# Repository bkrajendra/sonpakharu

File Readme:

##README
./hardware - PCB design files
./software - Firmware source code

To open source code:
cd software
code .

To open PCB design:
cd hardware
Open the sonpakharu.kicad_pro file with KiCad

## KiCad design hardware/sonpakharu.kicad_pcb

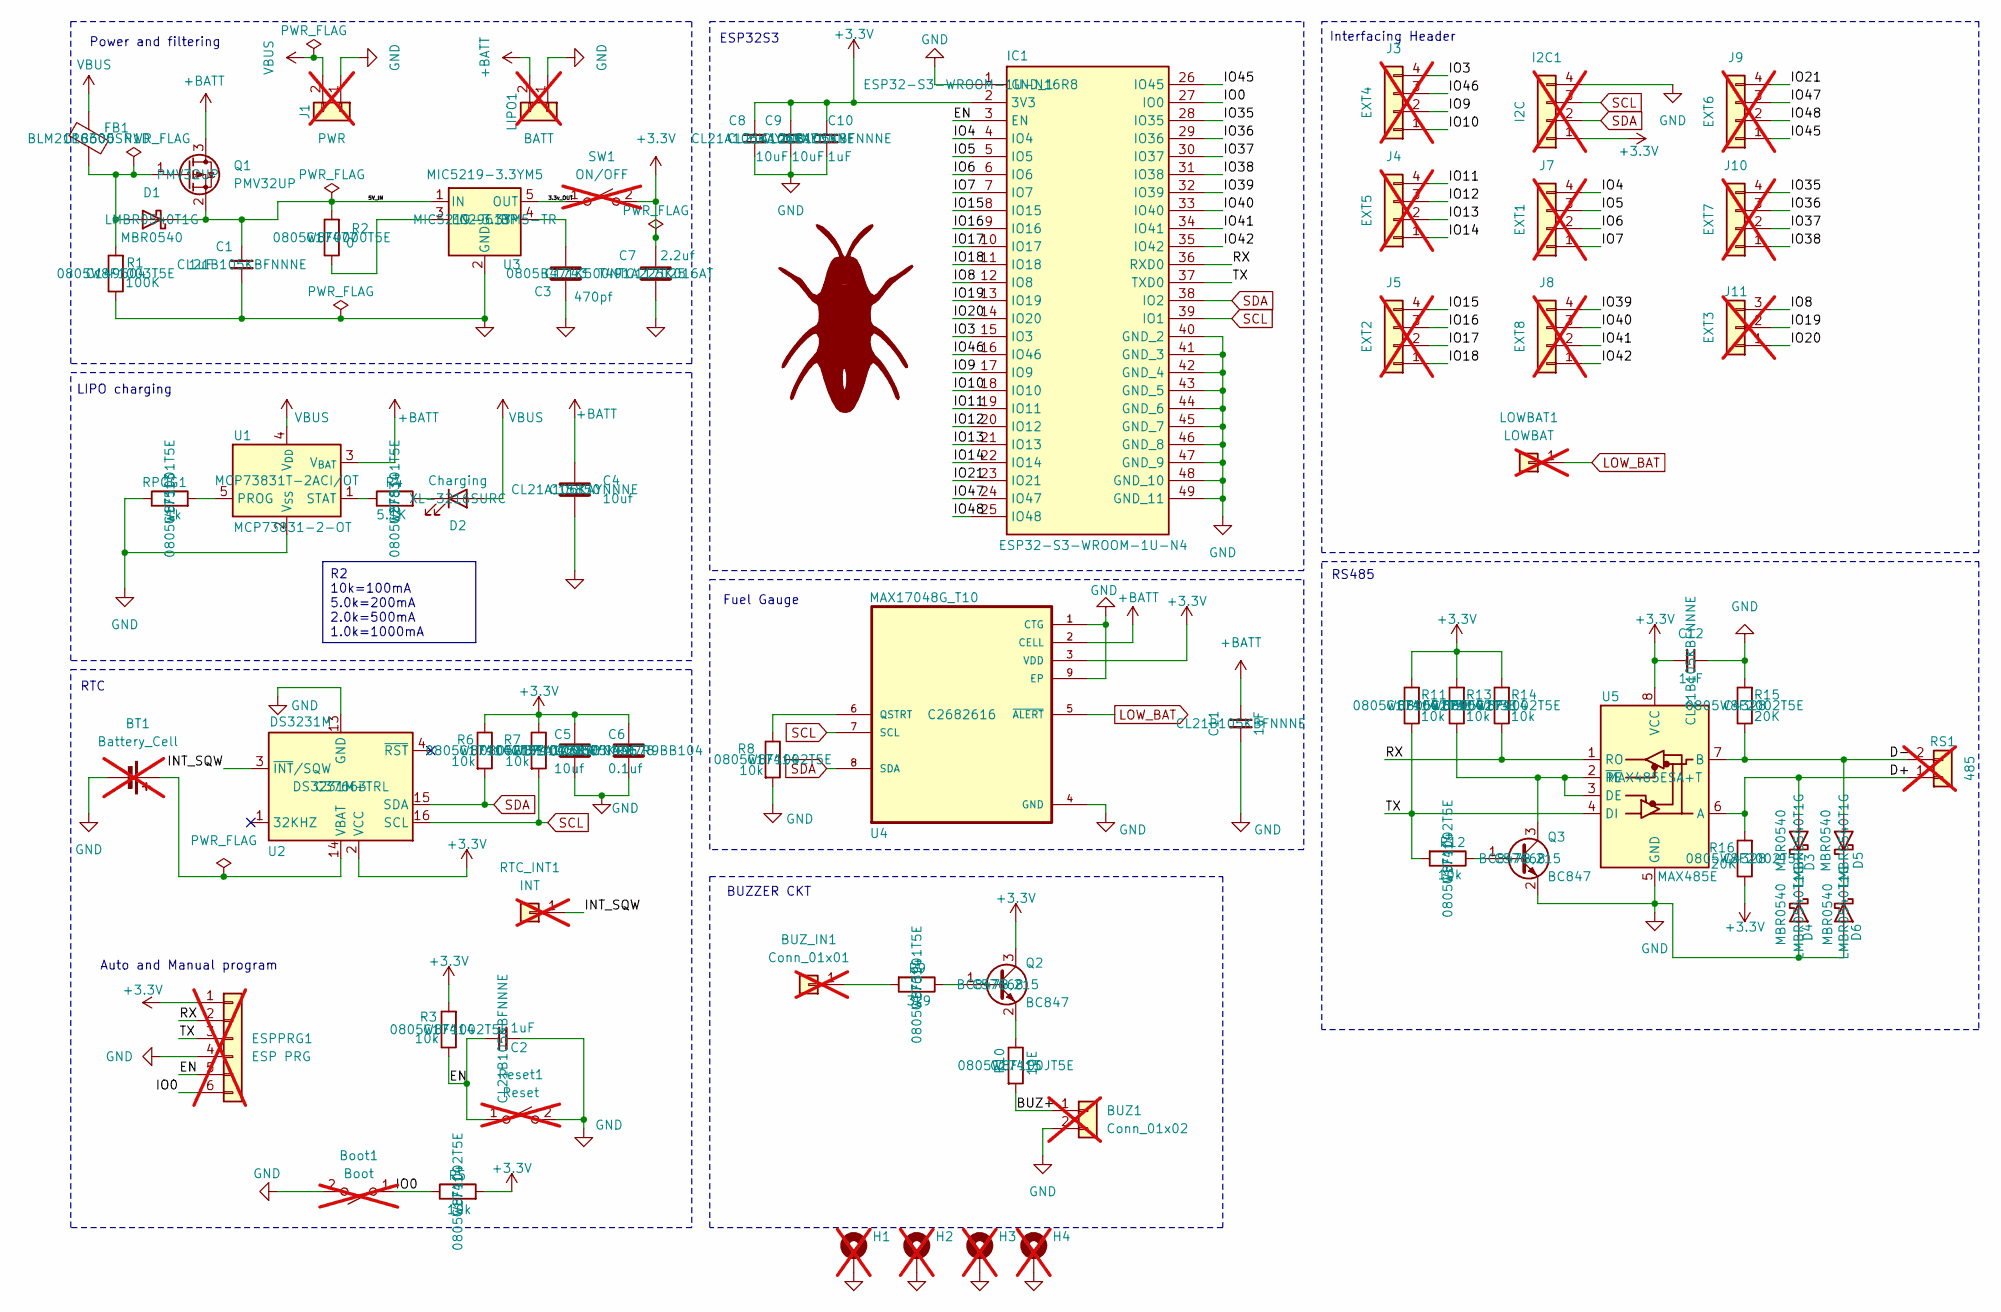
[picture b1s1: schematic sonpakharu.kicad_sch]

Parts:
BT1: Battery_Cell; BatteryHolder_Keystone_3002_1x2032; not fitted
BUZ1: Conn_01x02; PinHeader_1x02_P2.54mm_Vertical; not fitted
BUZ_IN1: Conn_01x01; PinHeader_1x01_P2.54mm_Vertical; not fitted
Boot1: Boot; TACTILE SWITCH 3X4X2MM SMD; not fitted
C1, C2, C10, C11, C12: 1uF; C_0805_2012Metric; MPN C28323
C3: 470pf; C_0805_2012Metric; MPN C1743
C4, C5: 10uf; C_0805_2012Metric; MPN C15850
C6: 0.1uf; C_0805_2012Metric; MPN C49678
C7: 2.2uf; CP_EIA-2012-12_Kemet-R_Pad1.30x1.05mm_HandSolder; MPN C117025
C8, C9: 10uF; C_0805_2012Metric; MPN C15850
D1, D3, D4, D5, D6: MBR0540; D_SOD-123; MPN C78545
D2: Charging; LED_1206_3216Metric; MPN C965822
ESPPRG1: ESP PRG; PinHeader_1x06_P2.54mm_Vertical; not fitted
FB1: FerriteBead; L_0805_2012Metric; MPN C18305
H1, H2, H4: MountingHole_Pad; MountingHole_3mm_Pad_Via; not fitted
H3: mounting hole; MountingHole_3mm_Pad_Via; not fitted
I2C1: I2C; PinHeader_1x04_P2.54mm_Vertical; not fitted
IC1: ESP32-S3-WROOM-1U-N4; ESP32S3WROOM1UN4; Manufacturer_Part_Number ESP32-S3-WROOM-1U-N4; Mouser Part Number 356-ESP32S3WROOM1UN4
J1: PWR; PinHeader_1x02_P2.54mm_Vertical; not fitted
J3: EXT4; PinHeader_1x04_P2.54mm_Vertical; not fitted
J4: EXT5; PinHeader_1x04_P2.54mm_Vertical; not fitted
J5: EXT2; PinHeader_1x04_P2.54mm_Vertical; not fitted
J7: EXT1; PinHeader_1x04_P2.54mm_Vertical; not fitted
J8: EXT8; PinHeader_1x04_P2.54mm_Vertical; not fitted
J9: EXT6; PinHeader_1x04_P2.54mm_Vertical; not fitted
J10: EXT7; PinHeader_1x04_P2.54mm_Vertical; not fitted
J11: EXT3; PinHeader_1x03_P2.54mm_Vertical; not fitted
LIPO1: BATT; PinHeader_1x02_P2.54mm_Vertical; not fitted
LOWBAT1: LOWBAT; PinHeader_1x01_P2.54mm_Vertical; not fitted
Q1: PMV32UP; SOT-23; MPN C2959851
Q2, Q3: BC847; SOT-23; MPN C57668
R1: 100K; R_0805_2012Metric; MPN C149504
R2: 0; R_0805_2012Metric; MPN C17477
R3, R5, R6, R7, R8, R11, R12, R13, R14: 10k; R_0805_2012Metric; MPN C17414
R4: 5.1K; R_0805_2012Metric; MPN C27834
R9: 3k9; R_0805_2012Metric; MPN C17614
R10: 10E; R_0805_2012Metric; MPN C17415
R15, R16: 20K; R_0805_2012Metric; MPN C4328
RPOG1: 1k; R_0805_2012Metric; MPN C17513
RS1: 485; PinHeader_1x02_P2.54mm_Vertical; not fitted
RTC_INT1: INT; PinHeader_1x01_P2.54mm_Vertical; not fitted
Reset1: Reset; TACTILE SWITCH 3X4X2MM SMD; not fitted
SW1: ON/OFF; PinHeader_1x02_P2.54mm_Vertical; not fitted
U1: MCP73831-2-OT; SOT-23-5; MPN C424093
U2: DS3231M; SOIC-16W_7.5x10.3mm_P1.27mm; MPN C37663
U3: MIC5219-3.3YM5; SOT-23-5; MPN C29613
U4: MAX17048G_T10; SON50P200X200X80-9N; MPN C2682616
U5: MAX485E; SOIC-8_3.9x4.9mm_P1.27mm; MPN C19738

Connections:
+3.3V: C5.1, C6.1, C7.1, C8.1, C9.1, C10.1, C12.2, ESPPRG1.1, I2C1.1, IC1.2 (3V3), Q2.3 (C), R3.2, R5.2, R6.1, R7.1, R11.2, R13.2, R14.2, R16.1, SW1.2 (B), U2.2 (VCC), U4.3 (VDD), U5.8 (VCC)
+BATT: C4.1, C11.1, LIPO1.2, Q1.3 (D), U1.3 (V_{BAT}), U4.2 (CELL)
/3.3v_OUT: SW1.1 (A), U3.5 (OUT)
/5V_IN: C1.1, D1.1 (K), Q1.2 (S), R2.2, U3.1 (IN)
/BUZ+: BUZ1.1, R10.2
/D+: D3.2 (A), R16.2, RS1.1, U5.6 (A); also elsewhere on the board
/D-: D5.2 (A), R15.1, RS1.2, U5.7 (B); also elsewhere on the board
/EN: C2.1, ESPPRG1.5, IC1.3 (EN), R3.1, Reset1.1 (A)
/INT_SQW: RTC_INT1.1, U2.3 (~INT/SQW)
/IO0: Boot1.1 (A), ESPPRG1.6, IC1.27 (IO0), R5.1
/IO3: IC1.15 (IO3), J3.4
/IO4: IC1.4 (IO4), J7.4
/IO5: IC1.5 (IO5), J7.3
/IO6: IC1.6 (IO6), J7.2
/IO7: IC1.7 (IO7), J7.1
/IO8: IC1.12 (IO8), J11.3
/IO9: IC1.17 (IO9), J3.2
/IO10: IC1.18 (IO10), J3.1
/IO11: IC1.19 (IO11), J4.4
/IO12: IC1.20 (IO12), J4.3
/IO13: IC1.21 (IO13), J4.2
/IO14: IC1.22 (IO14), J4.1
/IO15: IC1.8 (IO15), J5.4
/IO16: IC1.9 (IO16), J5.3
/IO17: IC1.10 (IO17), J5.2
/IO18: IC1.11 (IO18), J5.1
/IO19: IC1.13 (IO19), J11.2
/IO20: IC1.14 (IO20), J11.1
/IO21: IC1.23 (IO21), J9.4
/IO35: IC1.28 (IO35), J10.4
/IO36: IC1.29 (IO36), J10.3
/IO37: IC1.30 (IO37), J10.2
/IO38: IC1.31 (IO38), J10.1
/IO39: IC1.32 (IO39), J8.4
/IO40: IC1.33 (IO40), J8.3
/IO41: IC1.34 (IO41), J8.2
/IO42: IC1.35 (IO42), J8.1
/IO45: IC1.26 (IO45), J9.1
/IO46: IC1.16 (IO46), J3.3
/IO47: IC1.24 (IO47), J9.3
/IO48: IC1.25 (IO48), J9.2
/RX: ESPPRG1.2, IC1.36 (RXD0), R14.1, U5.1 (RO)
/TX: ESPPRG1.3, IC1.37 (TXD0), R11.1, R12.2, U5.4 (DI)
GND: BT1.2 (-), BUZ1.2, Boot1.2 (B), C1.2, C2.2, C3.2, C4.2, C5.2, C6.2, C7.2, C8.2, C9.2, C10.2, C11.2, C12.1, D4.2 (A), D6.2 (A), ESPPRG1.4, H1.1, H2.1, H3.1, H4.1, I2C1.4, IC1.1 (GND_1), IC1.40 (GND_2), IC1.41 (GND_3), IC1.42 (GND_4), IC1.43 (GND_5), IC1.44 (GND_6), IC1.45 (GND_7), IC1.46 (GND_8), IC1.47 (GND_9), IC1.48 (GND_10), IC1.49 (GND_11), J1.1, LIPO1.1, Q3.2 (E), R1.1, R8.2, R15.2, RPOG1.1, Reset1.2 (B), U1.2 (V_{SS}), U2.5 (GND), U2.6 (GND), U2.7 (GND), U2.8 (GND), U2.9 (GND), U2.10 (GND), U2.11 (GND), U2.12 (GND), U2.13 (GND), U3.2 (GND), U4.1 (CTG), U4.4 (GND), U4.9 (EP), U5.5 (GND)
LOW_BAT: LOWBAT1.1, U4.5 (~ALERT); also elsewhere on the board
unnamed: BT1.1 (+), U2.14 (VBAT)
unnamed 46: BUZ_IN1.1, R9.2; also elsewhere on the board
unnamed 47: D1.2 (A), FB1.2, Q1.1 (G), R1.2; also elsewhere on the board
unnamed: D2.1 (K), R4.2
unnamed: D3.1 (K), D4.1 (K)
unnamed: D5.1 (K), D6.1 (K)
unnamed: Q2.1 (B), R9.1
unnamed: Q2.2 (E), R10.1
unnamed: Q3.1 (B), R12.1
unnamed: Q3.3 (C), R13.1, U5.2 (~RE), U5.3 (DE)
unnamed: RPOG1.2, U1.5 (PROG)
unnamed: R4.1, U1.1 (STAT)
unnamed: C3.1, U3.4 (BP)
unnamed: R2.1, U3.3 (EN)
unnamed: R8.1, U4.6 (QSTRT)
SCL: I2C1.3, IC1.39 (IO1), R7.2, U2.16 (SCL), U4.7 (SCL)
SDA: I2C1.2, IC1.38 (IO2), R6.2, U2.15 (SDA), U4.8 (SDA)
VBUS: D2.2 (A), FB1.1, J1.2, U1.4 (V_{DD}); also elsewhere on the board

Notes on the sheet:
Power and filtering
BUZZER CKT
Auto and Manual program
Fuel Gauge
RS485
RTC
LIPO charging
ESP32S3
Interfacing Header
R2 10k=100mA 5.0k=200mA 2.0k=500mA 1.0k=1000mA

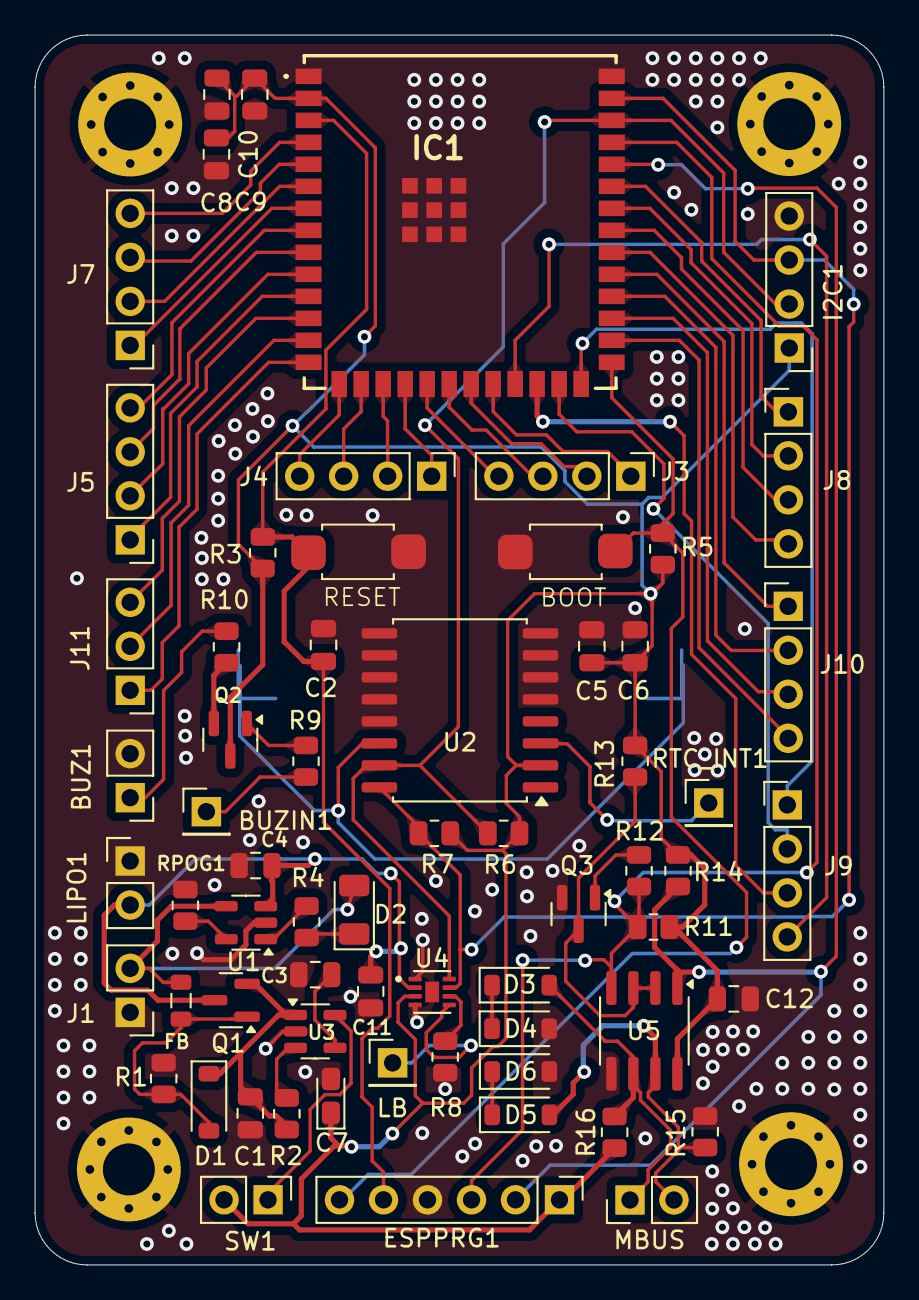
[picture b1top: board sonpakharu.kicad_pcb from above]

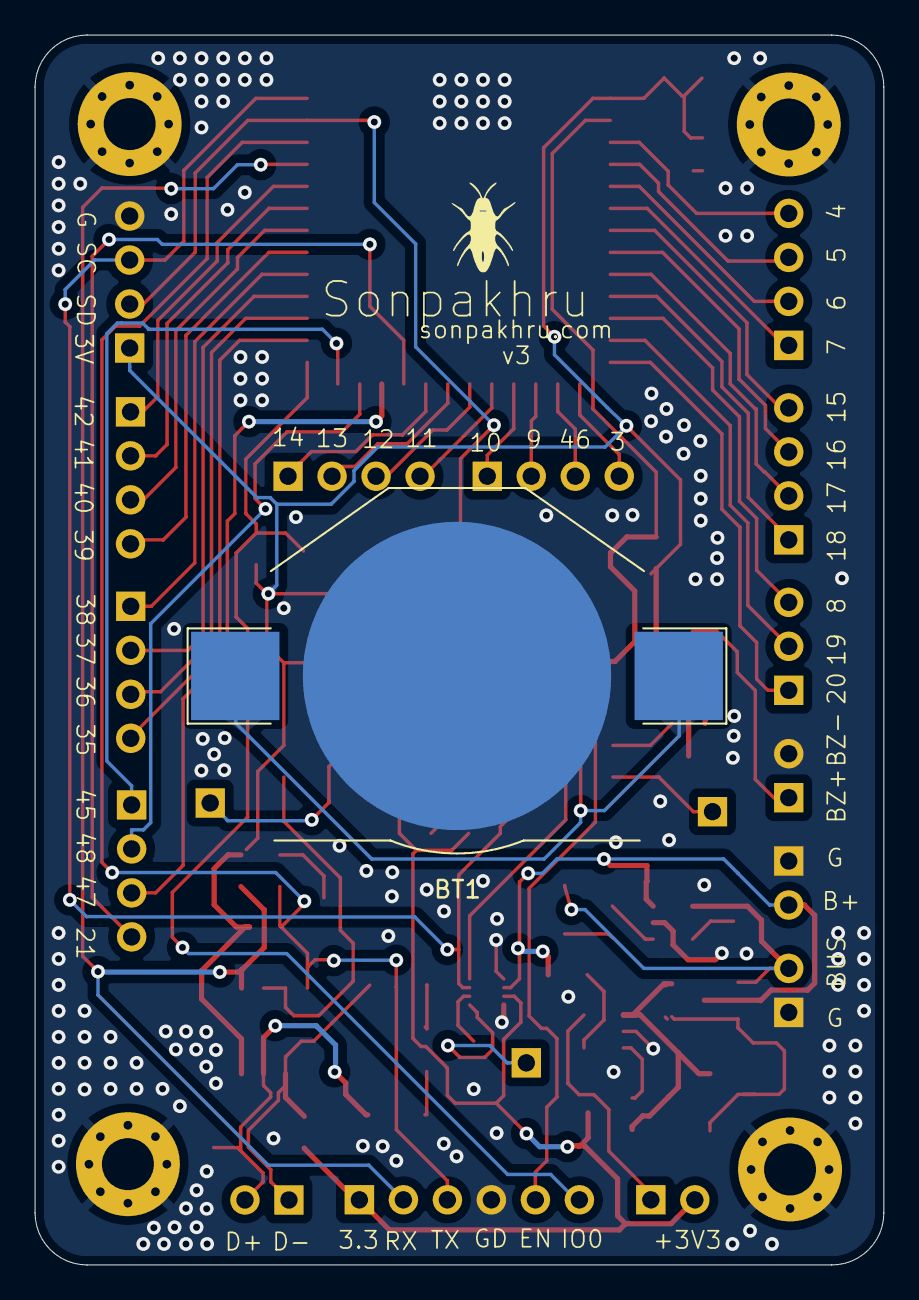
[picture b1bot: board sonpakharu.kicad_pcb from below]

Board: 2 copper layers, 49.0 x 71.0 mm, 71 parts (2 on the bottom side), 63 nets.

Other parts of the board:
BUZIN1: Conn_01x01; PinHeader_1x01_P2.54mm_Vertical
FB: FerriteBead; L_0805_2012Metric
LB: LOWBAT; PinHeader_1x01_P2.54mm_Vertical
MBUS: 485; PinHeader_1x02_P2.54mm_Vertical
spb: LOGO; sonpakaharu

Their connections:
/D+: MBUS.1; also elsewhere on the board
/D-: MBUS.2; also elsewhere on the board
LOW_BAT: LB.1; also elsewhere on the board
unnamed 46: BUZIN1.1; also elsewhere on the board
unnamed 47: FB.2; also elsewhere on the board
VBUS: FB.1; also elsewhere on the board

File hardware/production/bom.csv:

Designator,Footprint,Quantity,Value,LCSC Part #
BOOT1,TACTILE SWITCH 3X4X2MM SMD,1,Boot,
BT1,BatteryHolder_Keystone_3002_1x2032,1,Battery_Cell,
BUZ1,PinHeader_1x02_P2.54mm_Vertical,1,Conn_01x02,
BUZIN1,PinHeader_1x01_P2.54mm_Vertical,1,Conn_01x01,
C1,0805,1,1uF,C5137578
"C10, C11, C12, C2",0805,4,1uF,C363560
C3,0805,1,470pf,
"C4, C5",0805,2,10uf,
C6,0805,1,0.1uf,
C7,CP_EIA-2012-12_Kemet-R_Pad1.30x1.05mm_HandSolder,1,2.2uf,
"C8, C9",0805,2,10uF,C5137578
"D1, D3, D4, D5, D6",D_SOD-123,5,MBR0540,C116159
D2,1206,1,Charging,C779453
ESPPRG1,PinHeader_1x06_P2.54mm_Vertical,1,ESP PRG,
FB,0805,1,FerriteBead,
I2C1,PinHeader_1x04_P2.54mm_Vertical,1,I2C,
IC1,ESP32S3WROOM1UN4,1,ESP32-S3-WROOM-1U-N4,C3013945
J1,PinHeader_1x02_P2.54mm_Vertical,1,PWR,
J10,PinHeader_1x04_P2.54mm_Vertical,1,EXT7,
J11,PinHeader_1x03_P2.54mm_Vertical,1,EXT3,
J3,PinHeader_1x04_P2.54mm_Vertical,1,EXT4,
J4,PinHeader_1x04_P2.54mm_Vertical,1,EXT5,
J5,PinHeader_1x04_P2.54mm_Vertical,1,EXT2,
J7,PinHeader_1x04_P2.54mm_Vertical,1,EXT1,
J8,PinHeader_1x04_P2.54mm_Vertical,1,EXT8,
J9,PinHeader_1x04_P2.54mm_Vertical,1,EXT6,
LB,PinHeader_1x01_P2.54mm_Vertical,1,LOWBAT,
LIPO1,PinHeader_1x02_P2.54mm_Vertical,1,BATT,
MBUS,PinHeader_1x02_P2.54mm_Vertical,1,485,
Q1,SOT-23,1,PMV32UP,C96616
"Q2, Q3",SOT-23,2,BC847,
R1,0805,1,100K,
R10,0805,1,10E,
"R11, R12, R13, R14, R3, R5, R6, R7, R8",0805,9,10k,
"R15, R16",0805,2,20K,
R2,0805,1,0,
R4,0805,1,5.1K,
R9,0805,1,3k9,
RESET1,TACTILE SWITCH 3X4X2MM SMD,1,Reset,
RPOG1,0805,1,1k,
RTC_INT1,PinHeader_1x01_P2.54mm_Vertical,1,INT,
SW1,PinHeader_1x02_P2.54mm_Vertical,1,ON/OFF,
U1,SOT-23-5,1,MCP73831-2-OT,C424093
U2,SOIC-16W_7.5x10.3mm_P1.27mm,1,DS3231M,
U3,SOT-23-5,1,MIC5219-3.3YM5,
U4,SON50P200X200X80-9N,1,MAX17048G_T10,
U5,SOIC-8_3.9x4.9mm_P1.27mm,1,MAX485E,C19738

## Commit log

2023-12-01 Added s3 footprint
2023-12-01 Fixed paths
2023-12-02 added usb otg
2023-12-02 added uart,reset
2023-12-02 minor changes
2023-12-02 added image
2023-12-02 added power and program ckt
2023-12-02 Added Datasheet
2023-12-02 added adc
2023-12-02 added gpio connectors
2023-12-02 added battery connector
2023-12-02 main power
2023-12-02 khope ka kida
2023-12-02 minor change
2023-12-03 added gitifnore
2023-12-03 added main components mpn
2024-01-01 Fix: routing
2024-01-01 routing done
2024-01-02 added 485
2024-01-02 converted 485 sch to pcb
2024-01-02 component placment done
2024-01-02 all routing done, no errors, 3 minor warnings
2024-01-02 corrected placement
2024-01-02 track correction and tactile switch footprint pending
2024-01-03 almost all tracks corrected, added tactile smd
2024-01-03 all tracks corrected, 0 errors 0 warnings
2024-01-03 Added: labels
2024-01-03 completed all labels, added mx485 mpn
2024-01-03 corrected labels
2024-01-04 added holes
2024-01-07 Fix: added pads, ground vias and logo
2024-01-08 updated tactile smd part number
2024-02-04 Fix: foot prints, re routed pcb, added 3d model
2024-04-07 Fix: final fixes
2024-04-07 Fix cleanup
2024-04-15 rectified sch
2024-04-23 latest
2024-04-23 deleted unused footprints
2024-05-12 removed auto prg ckt, done routing, touch up pending
2024-05-13 corrected signal tracks
2024-06-04 rectified sda scl lines
2024-06-08 Create README.md
    Updated readme
2024-06-08 Readme 2
    README
2024-06-21 added IO4 pin to connector
2024-06-26 rectified labels, all routing done
2024-07-11 Fix: layout u[dated
2024-08-12 Added: rtc, fuel gauge, fixed placement, charge led and minor fixes
2024-08-13 Fix: directory structure chaned
2024-09-09 Fix: removed adc from board, minor chnages
2024-09-09 updated sch and components placement
2024-09-09 Fix: updated buzzer and board baundary
2024-09-10 routing done, tracks to optimize further
2024-09-10 routing complete, tracs optimization pending
2024-09-11 most tracks optimized, silkscreen warnings pending
2024-10-14 Rerouted the board
2025-02-08 Fix: updates
2025-07-19 Fix: new changes
2025-07-19 doc updated
